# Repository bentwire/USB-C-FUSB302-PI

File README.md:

# USB-C-FUSB302-PI

KiCad files for dev board FUSB302B+RP2040

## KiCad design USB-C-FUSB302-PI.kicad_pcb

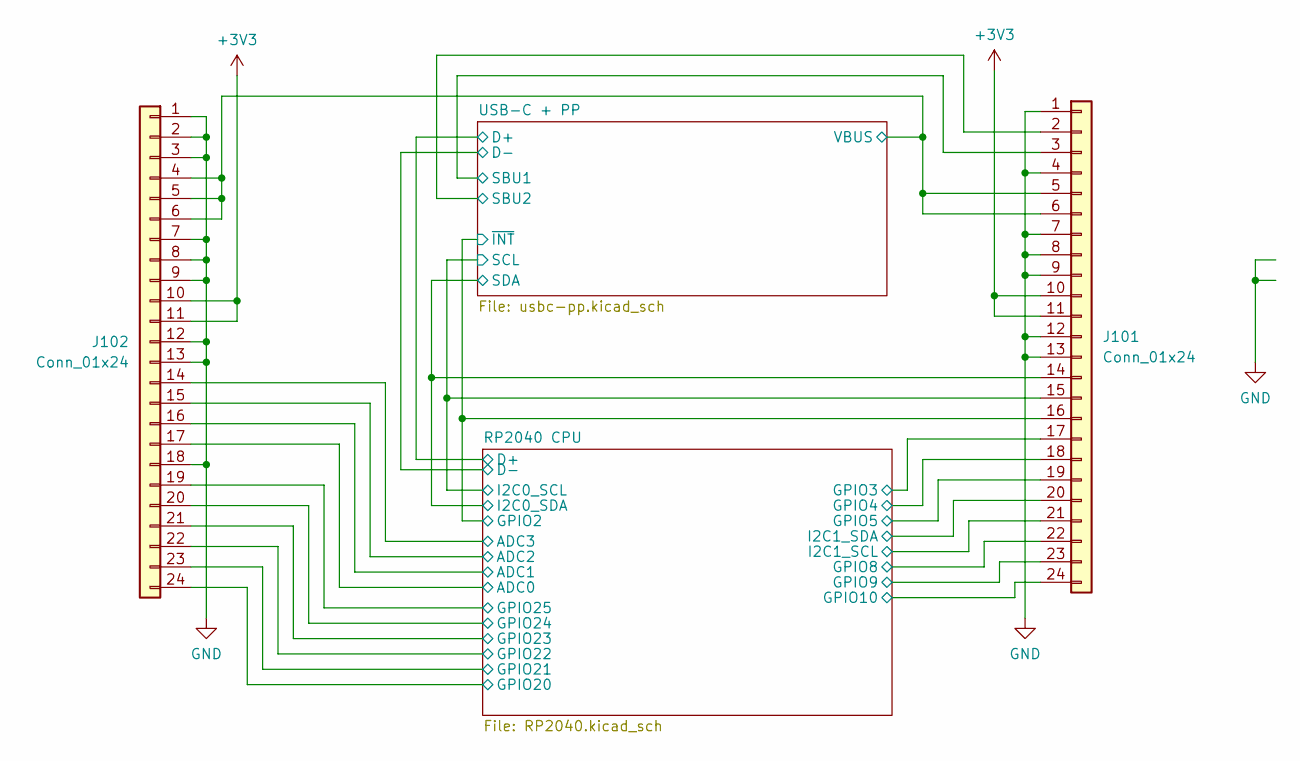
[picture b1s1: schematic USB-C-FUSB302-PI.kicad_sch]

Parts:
J101, J102: Conn_01x24; PinHeader_1x24_P2.54mm_Vertical

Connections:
+3V3: J101.10, J101.11, J102.10, J102.11; also elsewhere on the board
/RP2040 CPU/ADC0: J102.17; also elsewhere on the board
/RP2040 CPU/ADC1: J102.16; also elsewhere on the board
/RP2040 CPU/ADC2: J102.15; also elsewhere on the board
/RP2040 CPU/ADC3: J102.14; also elsewhere on the board
/RP2040 CPU/GPIO2: J101.16; also elsewhere on the board
/RP2040 CPU/GPIO3: J101.17; also elsewhere on the board
/RP2040 CPU/GPIO4: J101.18; also elsewhere on the board
/RP2040 CPU/GPIO5: J101.19; also elsewhere on the board
/RP2040 CPU/GPIO8: J101.22; also elsewhere on the board
/RP2040 CPU/GPIO9: J101.23; also elsewhere on the board
/RP2040 CPU/GPIO10: J101.24; also elsewhere on the board
/RP2040 CPU/GPIO20: J102.24; also elsewhere on the board
/RP2040 CPU/GPIO21: J102.23; also elsewhere on the board
/RP2040 CPU/GPIO22: J102.22; also elsewhere on the board
/RP2040 CPU/GPIO23: J102.21; also elsewhere on the board
/RP2040 CPU/GPIO24: J102.20; also elsewhere on the board
/RP2040 CPU/GPIO25: J102.19; also elsewhere on the board
/RP2040 CPU/I2C0_SCL: J101.15; also elsewhere on the board
/RP2040 CPU/I2C0_SDA: J101.14; also elsewhere on the board
/RP2040 CPU/I2C1_SCL: J101.21; also elsewhere on the board
/RP2040 CPU/I2C1_SDA: J101.20; also elsewhere on the board
/USB-C + PP/SBU1: J101.3; also elsewhere on the board
/USB-C + PP/SBU2: J101.2; also elsewhere on the board
/USB-C + PP/VBUS: J101.5, J101.6, J102.4, J102.5, J102.6; also elsewhere on the board
GND: J101.1, J101.4, J101.7, J101.8, J101.9, J101.12, J101.13, J102.1, J102.2, J102.3, J102.7, J102.8, J102.9, J102.12, J102.13, J102.18; also elsewhere on the board

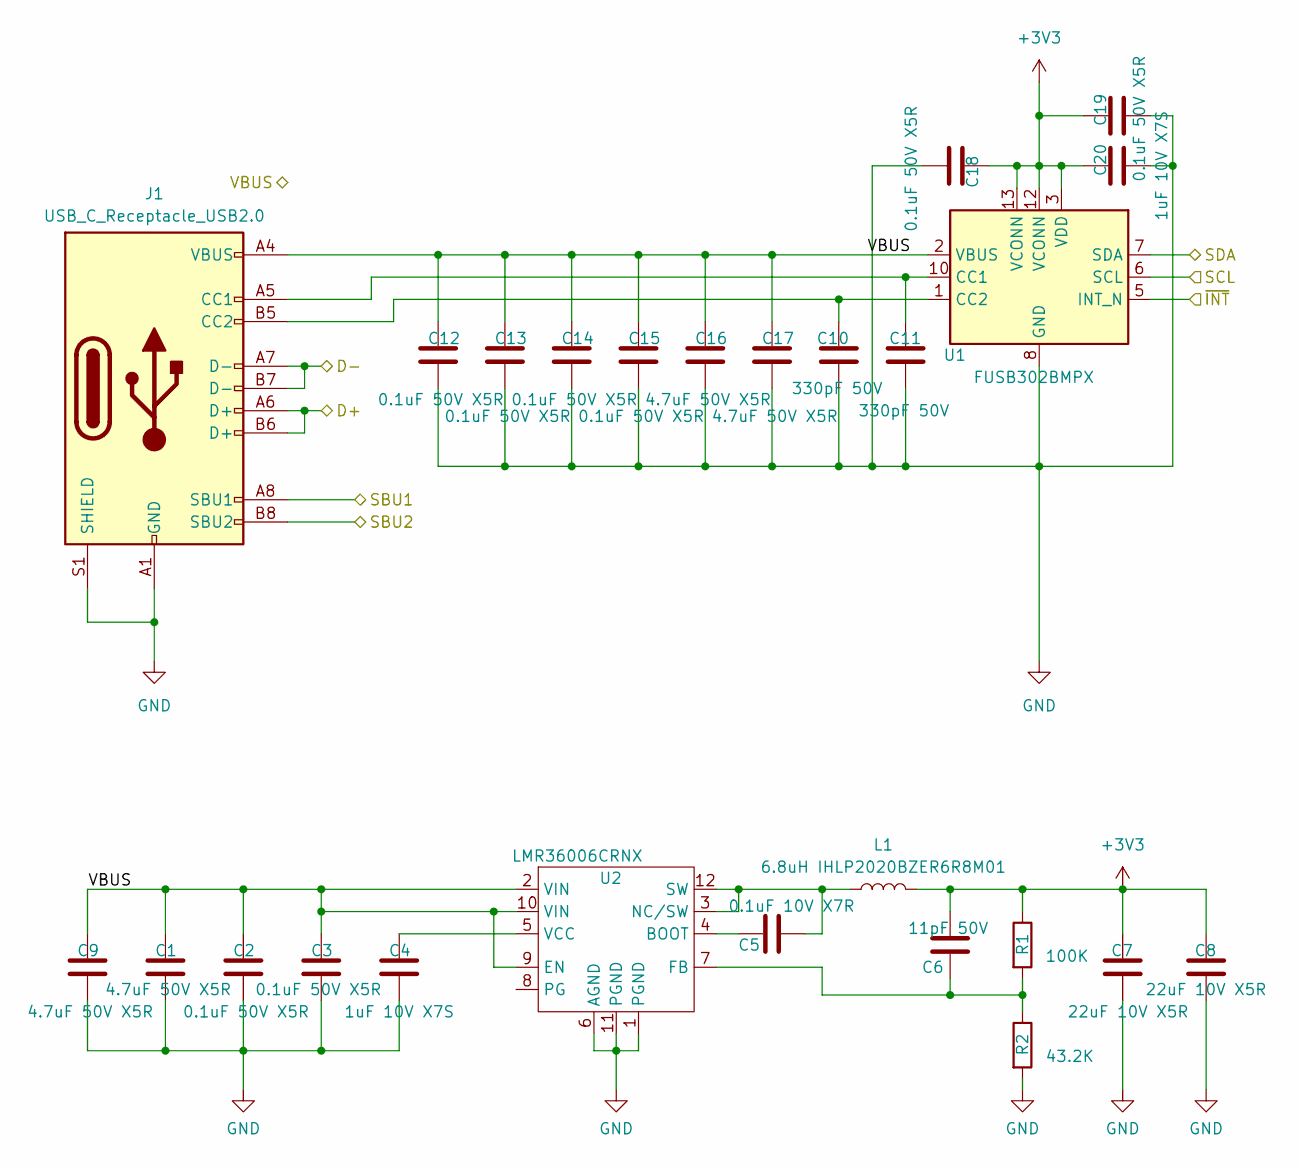
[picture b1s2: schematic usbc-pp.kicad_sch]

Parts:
C1, C9, C16, C17: 4.7uF 50V X5R; C_0805_2012Metric
C2, C3, C12, C13, C14, C15, C18, C19: 0.1uF 50V X5R; C_0402_1005Metric
C4, C20: 1uF 10V X7S; C_0402_1005Metric
C5: 0.1uF 10V X7R; C_0402_1005Metric
C6: 11pF 50V; C_0402_1005Metric
C7, C8: 22uF 10V X5R; C_0805_2012Metric
C10, C11: 330pF 50V; C_0402_1005Metric
J1: USB_C_Receptacle_USB2.0; USB_C_Receptacle_GCT_USB4105-xx-A_16P_TopMnt_Horizontal
L1: 6.8uH IHLP2020BZER6R8M01; L_Vishay_IHLP-2020; MPN 74405042100
R1: 100K; R_0402_1005Metric
R2: 43.2K; R_0402_1005Metric
U1: FUSB302BMPX; WQFN-14-1EP_2.5x2.5mm_P0.5mm_EP1.45x1.45mm
U2: LMR36006CRNX; TI-RNX0012A-VQFN-HR

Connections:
+3V3: C6.2, C7.2, C8.2, C18.1, C19.1, C20.1, L1.2, R1.1, U1.3 (VDD), U1.4 (VDD), U1.12 (VCONN), U1.13 (VCONN); also elsewhere on the board
/RP2040 CPU/D+: J1.A6 (D+), J1.B6 (D+); also elsewhere on the board
/RP2040 CPU/D-: J1.A7 (D-), J1.B7 (D-); also elsewhere on the board
/RP2040 CPU/GPIO2: U1.5 (INT_N); also elsewhere on the board
/RP2040 CPU/I2C0_SCL: U1.6 (SCL); also elsewhere on the board
/RP2040 CPU/I2C0_SDA: U1.7 (SDA); also elsewhere on the board
/USB-C + PP/SBU1: J1.A8 (SBU1); also elsewhere on the board
/USB-C + PP/SBU2: J1.B8 (SBU2); also elsewhere on the board
/USB-C + PP/VBUS: C1.1, C2.1, C3.1, C9.1, C12.1, C13.1, C14.1, C15.1, C16.1, C17.1, J1.A4 (VBUS), J1.A9 (VBUS), J1.B4 (VBUS), J1.B9 (VBUS), U1.2 (VBUS), U2.2 (VIN), U2.9 (EN), U2.10 (VIN); also elsewhere on the board
GND: C1.2, C2.2, C3.2, C4.2, C7.1, C8.1, C9.2, C10.1, C11.1, C12.2, C13.2, C14.2, C15.2, C16.2, C17.2, C18.2, C19.2, C20.2, J1.A1 (GND), J1.A12 (GND), J1.B1 (GND), J1.B12 (GND), J1.S1 (SHIELD), R2.2, U1.8 (GND), U1.9 (GND), U1.15 (GND), U2.1 (PGND), U2.6 (AGND), U2.11 (PGND); also elsewhere on the board
unnamed: C11.2, J1.A5 (CC1), U1.10 (CC1), U1.11 (CC1)
unnamed: C10.2, J1.B5 (CC2), U1.1 (CC2), U1.14 (CC2)
unnamed: C5.1, U2.4 (BOOT)
unnamed: C6.1, R1.2, R2.1, U2.7 (FB)
unnamed: C5.2, L1.1, U2.3 (NC/SW), U2.12 (SW)
unnamed: C4.1, U2.5 (VCC)

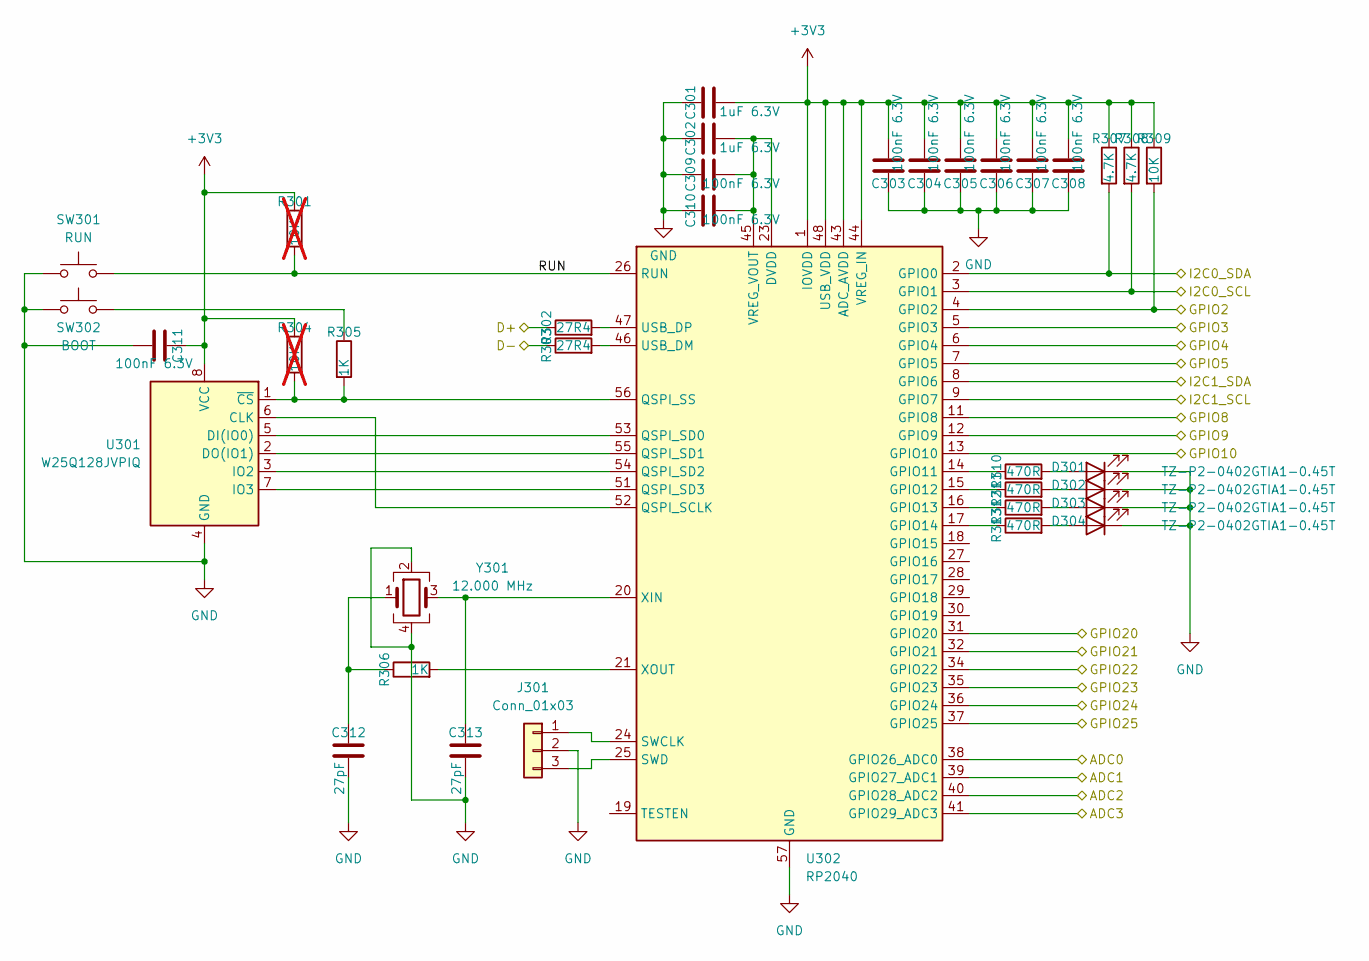
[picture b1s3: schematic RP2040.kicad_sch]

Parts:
C301, C302: 1uF 6.3V; C_0402_1005Metric
C303, C304, C305, C306, C307, C308, C309, C310, C311: 100nF 6.3V; C_0201_0603Metric
C312, C313: 27pF; C_0201_0603Metric
D301, D302, D303, D304: TZ-P2-0402GTIA1-0.45T; LED_0402_1005Metric
J301: Conn_01x03; PinHeader_1x03_P2.54mm_Vertical
R301, R304: 10K; R_0201_0603Metric; not fitted
R302, R303: 27R4; R_0201_0603Metric
R305, R306: 1K; R_0201_0603Metric
R307, R308: 4.7K; R_0201_0603Metric
R309: 10K; R_0201_0603Metric
R310, R311, R312, R313: 470R; R_0201_0603Metric
SW301: RUN; SW_SPST_Panasonic_EVQPL_3PL_5PL_PT_A15; Part EVQPLDA15
SW302: BOOT; SW_SPST_Panasonic_EVQPL_3PL_5PL_PT_A15; Part EVQPLDA15
U301: W25Q128JVPIQ; WSON-8-1EP_6x5mm_P1.27mm_EP3.4x4.3mm
U302: RP2040; QFN-56-1EP_7x7mm_P0.4mm_EP3.2x3.2mm
Y301: 12.000 MHz; Crystal_SMD_EuroQuartz_X22-4Pin_2.5x2.0mm

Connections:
+3V3: C301.2, C303.2, C304.2, C305.2, C306.2, C307.2, C308.2, C311.1, R301.1, R304.1, R307.1, R308.1, R309.1, U301.8 (VCC), U302.1 (IOVDD), U302.10 (IOVDD), U302.22 (IOVDD), U302.33 (IOVDD), U302.42 (IOVDD), U302.43 (ADC_AVDD), U302.44 (VREG_IN), U302.48 (USB_VDD), U302.49 (IOVDD); also elsewhere on the board
/RP2040 CPU/ADC0: U302.38 (GPIO26_ADC0); also elsewhere on the board
/RP2040 CPU/ADC1: U302.39 (GPIO27_ADC1); also elsewhere on the board
/RP2040 CPU/ADC2: U302.40 (GPIO28_ADC2); also elsewhere on the board
/RP2040 CPU/ADC3: U302.41 (GPIO29_ADC3); also elsewhere on the board
/RP2040 CPU/D+: R302.1; also elsewhere on the board
/RP2040 CPU/D-: R303.1; also elsewhere on the board
/RP2040 CPU/GPIO2: R309.2, U302.4 (GPIO2); also elsewhere on the board
/RP2040 CPU/GPIO3: U302.5 (GPIO3); also elsewhere on the board
/RP2040 CPU/GPIO4: U302.6 (GPIO4); also elsewhere on the board
/RP2040 CPU/GPIO5: U302.7 (GPIO5); also elsewhere on the board
/RP2040 CPU/GPIO8: U302.11 (GPIO8); also elsewhere on the board
/RP2040 CPU/GPIO9: U302.12 (GPIO9); also elsewhere on the board
/RP2040 CPU/GPIO10: U302.13 (GPIO10); also elsewhere on the board
/RP2040 CPU/GPIO20: U302.31 (GPIO20); also elsewhere on the board
/RP2040 CPU/GPIO21: U302.32 (GPIO21); also elsewhere on the board
/RP2040 CPU/GPIO22: U302.34 (GPIO22); also elsewhere on the board
/RP2040 CPU/GPIO23: U302.35 (GPIO23); also elsewhere on the board
/RP2040 CPU/GPIO24: U302.36 (GPIO24); also elsewhere on the board
/RP2040 CPU/GPIO25: U302.37 (GPIO25); also elsewhere on the board
/RP2040 CPU/I2C0_SCL: R308.2, U302.3 (GPIO1); also elsewhere on the board
/RP2040 CPU/I2C0_SDA: R307.2, U302.2 (GPIO0); also elsewhere on the board
/RP2040 CPU/I2C1_SCL: U302.9 (GPIO7); also elsewhere on the board
/RP2040 CPU/I2C1_SDA: U302.8 (GPIO6); also elsewhere on the board
/RP2040 CPU/RUN: R301.2, SW301.2, U302.26 (RUN)
GND: C301.1, C302.1, C303.1, C304.1, C305.1, C306.1, C307.1, C308.1, C309.1, C310.1, C311.2, C312.2, C313.2, D301.1 (K), D302.1 (K), D303.1 (K), D304.1 (K), J301.2, SW301.1, SW302.1, U301.4 (GND), U302.57 (GND), Y301.2, Y301.4; also elsewhere on the board
unnamed: C312.1, R306.1, Y301.1
unnamed: D301.2 (A), R310.2
unnamed: D302.2 (A), R311.2
unnamed: D303.2 (A), R312.2
unnamed: D304.2 (A), R313.2
unnamed: J301.1, U302.24 (SWCLK)
unnamed: J301.3, U302.25 (SWD)
unnamed: R305.1, SW302.2
unnamed: U301.6 (CLK), U302.52 (QSPI_SCLK)
unnamed: U301.5 (DI(IO0)), U302.53 (QSPI_SD0)
unnamed: U301.2 (DO(IO1)), U302.55 (QSPI_SD1)
unnamed: U301.3 (IO2), U302.54 (QSPI_SD2)
unnamed: U301.7 (IO3), U302.51 (QSPI_SD3)
unnamed: R304.2, R305.2, U301.1 (~CS), U302.56 (QSPI_SS)
unnamed: R310.1, U302.14 (GPIO11)
unnamed: R311.1, U302.15 (GPIO12)
unnamed: R312.1, U302.16 (GPIO13)
unnamed: R313.1, U302.17 (GPIO14)
unnamed: R303.2, U302.46 (USB_DM)
unnamed: R302.2, U302.47 (USB_DP)
unnamed: C302.2, C309.2, C310.2, U302.23 (DVDD), U302.45 (VREG_VOUT), U302.50 (DVDD)
unnamed: C313.1, U302.20 (XIN), Y301.3
unnamed: R306.2, U302.21 (XOUT)

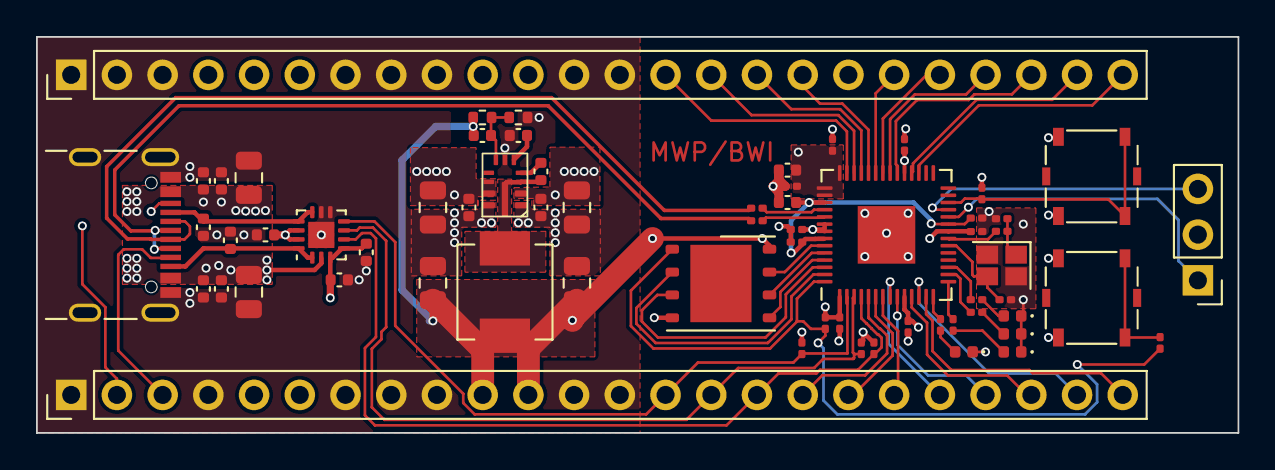
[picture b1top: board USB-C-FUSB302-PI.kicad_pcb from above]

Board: 4 copper layers, 66.8 x 22.0 mm, 64 parts (0 on the bottom side), 58 nets.

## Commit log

2023-10-06 Initial commit. This is what was sent to JLCPCB
2023-10-06 Add README...
2023-10-06 Create LICENSE
    Until I find something better.
2023-10-26 Create PDF's of design.
2023-12-20 3.3V Buck Regulator testing with PHC8-1035 20W USB-C PD charger 5V<->12V
